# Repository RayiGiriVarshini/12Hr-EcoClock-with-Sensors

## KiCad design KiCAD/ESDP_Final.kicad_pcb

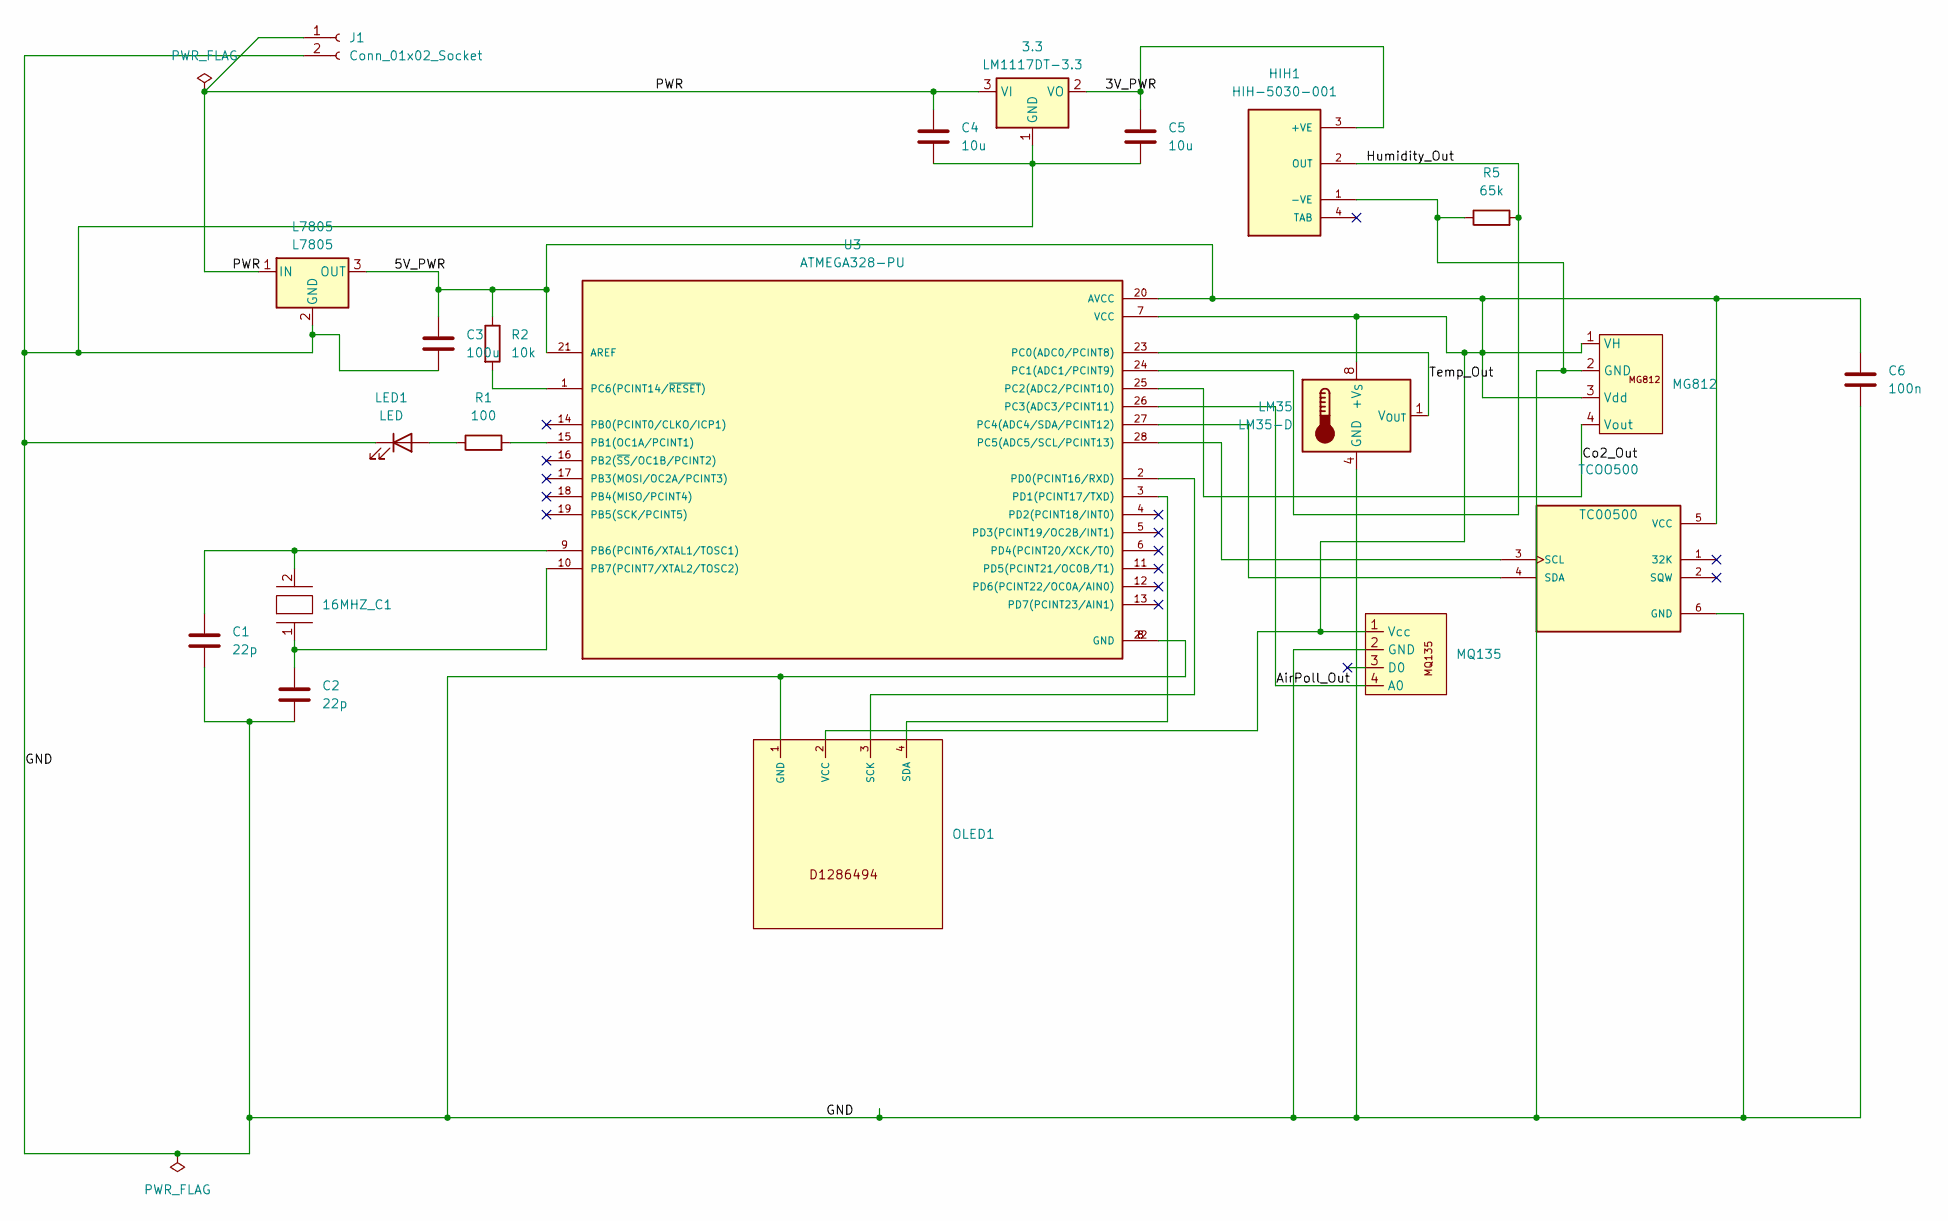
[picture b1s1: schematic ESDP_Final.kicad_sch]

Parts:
3.3: LM1117DT-3.3; TO-252-3_TabPin2
16MHZ_C1: 16MHzbygiri
C1, C2: 22p; C_0805_2012Metric_Pad1.18x1.45mm_HandSolder
C3: 100u; C_0805_2012Metric_Pad1.18x1.45mm_HandSolder
C4, C5: 10u; C_0805_2012Metric_Pad1.18x1.45mm_HandSolder
C6: 100n; C_0805_2012Metric_Pad1.18x1.45mm_HandSolder
HIH1: HIH-5030-001; HONEYWELL_HIH-5030-001
J1: Conn_01x02_Socket; PinSocket_1x02_P2.54mm_Vertical
L7805: L7805; TO-220-3_Vertical
LED1: LED; LED_0805_2012Metric
LM35: LM35-D; SOIC-8_3.9x4.9mm_P1.27mm
MG812: MG812_co2
MQ135: PinSocket_1x04_P2.54mm_Vertical
OLED1: PinSocket_1x04_P2.54mm_Vertical
R1: 100; R_0805_2012Metric_Pad1.20x1.40mm_HandSolder
R2: 10k; R_0805_2012Metric_Pad1.20x1.40mm_HandSolder
R5: 65k; R_0805_2012Metric_Pad1.20x1.40mm_HandSolder
TCOO500: TC00500; PinSocket_1x06_P2.54mm_Vertical; PARTREV N/A
U3: ATMEGA328-PU; DIP787W46P254L3467H508Q28; PARTREV B

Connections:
/3V_PWR: 3.3.2 (VO), C5.1, HIH1.3 (+VE)
/5V_PWR: C3.1, C6.1, L7805.3 (OUT), LM35.8 (+V_{S}), MG812.1 (VH), MG812.3 (Vdd), MQ135.1 (Vcc), OLED1.2 (VCC), R2.1, TCOO500.5 (VCC), U3.7 (VCC), U3.20 (AVCC), U3.21 (AREF)
/AirPoll_Out: MQ135.4 (A0), U3.26 (PC3(ADC3/PCINT11))
/Co2_Out: MG812.4 (Vout), U3.25 (PC2(ADC2/PCINT10))
/GND: 3.3.1 (GND), C1.2, C2.2, C3.2, C4.2, C5.2, C6.2, HIH1.1 (-VE), J1.2, L7805.2 (GND), LED1.1 (K), LM35.4 (GND), MG812.2 (GND), MQ135.2 (GND), OLED1.1 (GND), R5.1, TCOO500.6 (GND), U3.8 (GND), U3.22 (GND)
/Humidity_Out: HIH1.2 (OUT), R5.2, U3.24 (PC1(ADC1/PCINT9))
/PWR: 3.3.3 (VI), C4.1, J1.1, L7805.1 (IN)
/Temp_Out: LM35.1 (V_{OUT}), U3.23 (PC0(ADC0/PCINT8))
unnamed: LED1.2 (A), R1.1
unnamed: OLED1.3 (SCK), U3.2 (PD0(PCINT16/RXD))
unnamed: OLED1.4 (SDA), U3.3 (PD1(PCINT17/TXD))
unnamed: TCOO500.3 (SCL), U3.28 (PC5(ADC5/SCL/PCINT13))
unnamed: TCOO500.4 (SDA), U3.27 (PC4(ADC4/SDA/PCINT12))
unnamed: R1.2, U3.15 (PB1(OC1A/PCINT1))
unnamed: 16MHZ_C1.2, C1.1, U3.9 (PB6(PCINT6/XTAL1/TOSC1))
unnamed: 16MHZ_C1.1, C2.1, U3.10 (PB7(PCINT7/XTAL2/TOSC2))
unnamed: R2.2, U3.1 (PC6(PCINT14/~RESET))

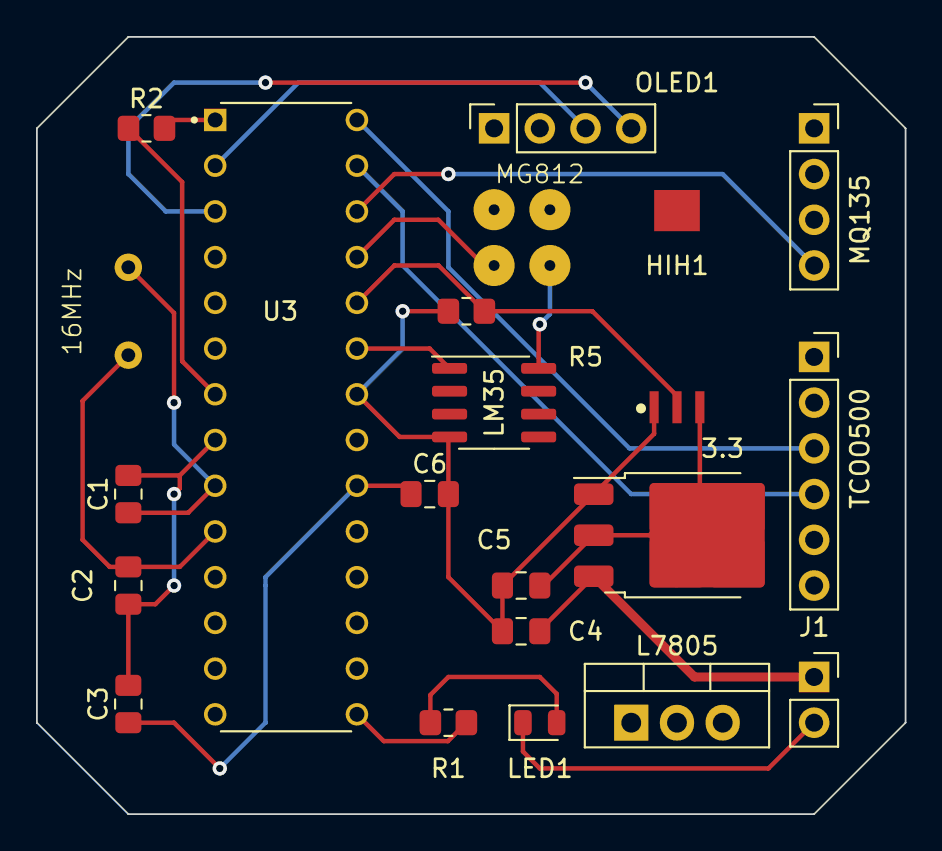
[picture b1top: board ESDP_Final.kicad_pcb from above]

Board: 4 copper layers, 48.3 x 43.2 mm, 21 parts (0 on the bottom side), 17 nets.

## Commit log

2025-07-18 Create raw
